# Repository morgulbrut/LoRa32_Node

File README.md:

# LoRa32 Node

A simple breakoutboard / antenna mount for those cool, inexpensive Heltec LoRa32.

some examples can be found over there: https://github.com/morgulbrut/LoRa32_Workshop

## Features

 * DHT11 sensor.
 * 18650 battery holder.
 * Shitty Addon Connector.
 * Piece to break out and use as an antenna mount.
 * Designed in the Canton of Glarus.

## TODO/Problems

There are some different Versions around which aren't not totally pin compatible on some power pins.

 * DHT11 are super inaccurate, replace with at least DHT21.
 * Add some 0R on those incompatible pins.
 * Add battery measurement.

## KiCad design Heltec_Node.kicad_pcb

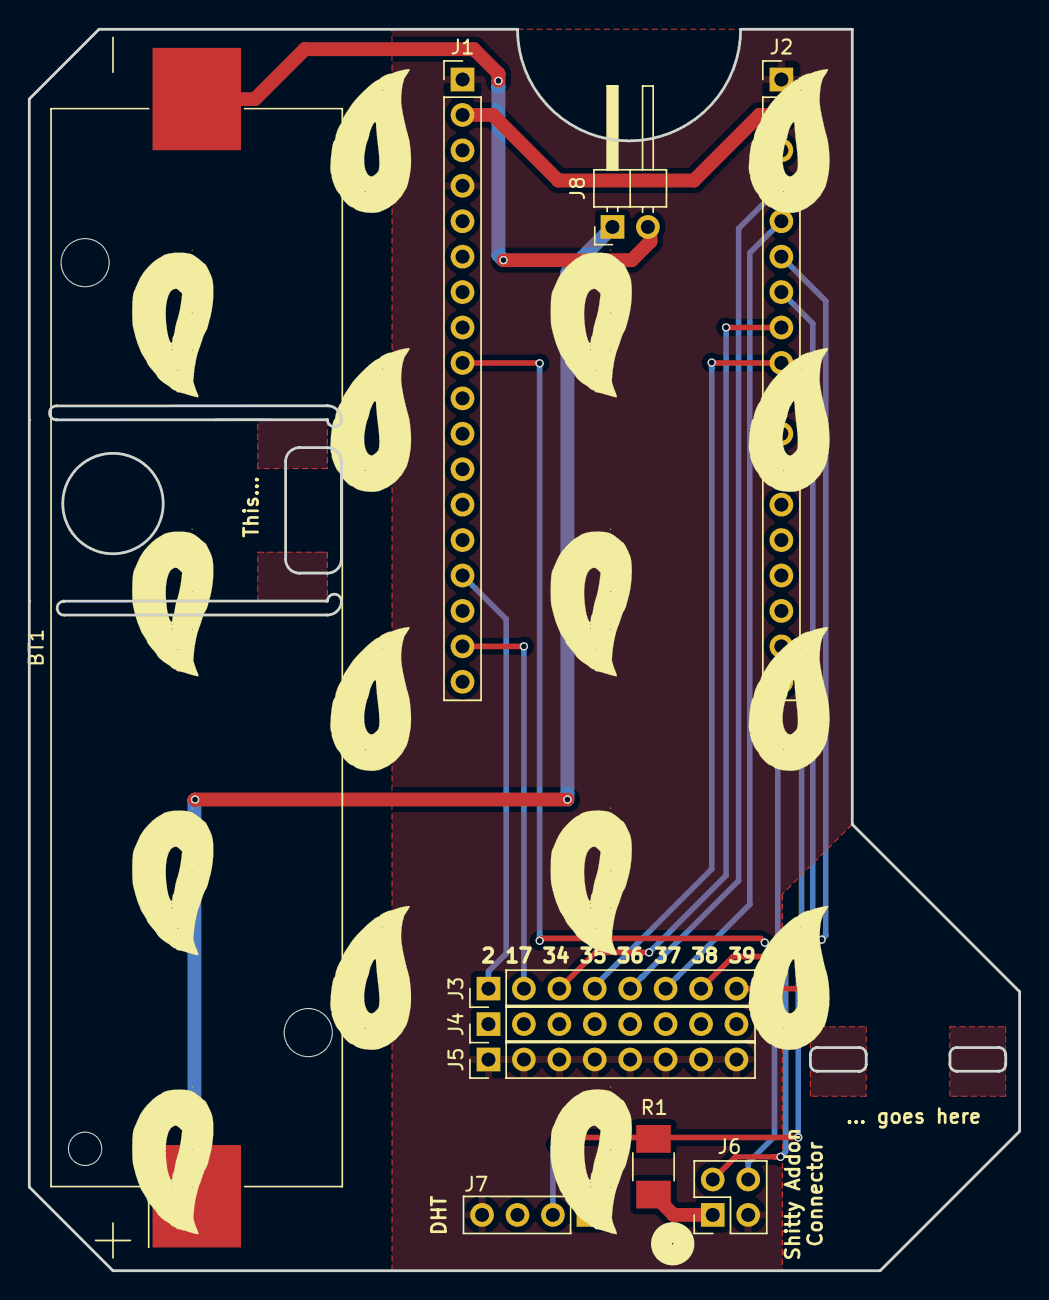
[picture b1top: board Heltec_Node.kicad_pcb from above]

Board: 2 copper layers, 71.0 x 89.0 mm, 10 parts (0 on the bottom side), 16 nets.

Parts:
BT1: Battery_Cell; Keystone_1042_1x18650
J1, J2: Conn_01x18_Female; Socket_Strip_Straight_1x18_Pitch2.54mm
J3, J4, J5: Conn_01x08; Pin_Header_Straight_1x08_Pitch2.54mm
J6: Conn_02x02_Top_Bottom; Pin_Header_Straight_2x02_Pitch2.54mm
J7: Conn_01x04; Pin_Header_Straight_1x04_Pitch2.54mm
J8: Conn_01x02; Pin_Header_Angled_1x02_Pitch2.54mm
R1: 5k1; R_1210_HandSoldering

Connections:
2: J1.15, J3.1
17: J1.17, J3.2
34: J2.8, J3.3
35: J2.9, J3.4
36: J2.4, J3.5
37: J2.5, J3.6
38: J2.6, J3.7
39: J2.7, J3.8
+3V3: J1.3, J2.3, J4.1, J4.2, J4.3, J4.4, J4.5, J4.6, J4.7, J4.8, J6.1, J7.1, R1.1
+5V: J1.2, J2.2
DHT_D: J2.17, J7.2, R1.2
GND: J1.1, J1.4, J2.1, J5.1, J5.2, J5.3, J5.4, J5.5, J5.6, J5.7, J5.8, J6.3, J7.4
unnamed: BT1.1, J8.1
unnamed: BT1.2, J8.2
SCL: J1.9, J6.4
SDA: J2.18, J6.2

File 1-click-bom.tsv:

References	Qty	Description	Manufacturer	MPN	Manufacturer	MPN	Digikey	Mouser	RS	Newark	Farnell
J1, J2	2	Female Header 2.54x18									
R1	1	Resistor 5k1  1210	Vishay	CRCW12105K10FKEAHP	Vishay	CRCW12105K10FKEA	CRCW12105K10FKEA-ND	71CRCW12105K10FKEAH		43AC0126	2802508
J3,J4,J5	3	Male Header 2.54x8									
J6	1	Male Header 2.54x2x2									
J5	1	DHT 11

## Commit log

2018-07-18 init
2018-07-18 Added bom
2018-07-20 removed unused files
2018-07-20 gitignore added
2018-12-01 added image
2018-12-01 Readme
2019-04-10 [ImgBot] Optimize images
    /imgs/IMG_6957.JPG -- 1,446.09kb -> 1,446.09kb (0%)
